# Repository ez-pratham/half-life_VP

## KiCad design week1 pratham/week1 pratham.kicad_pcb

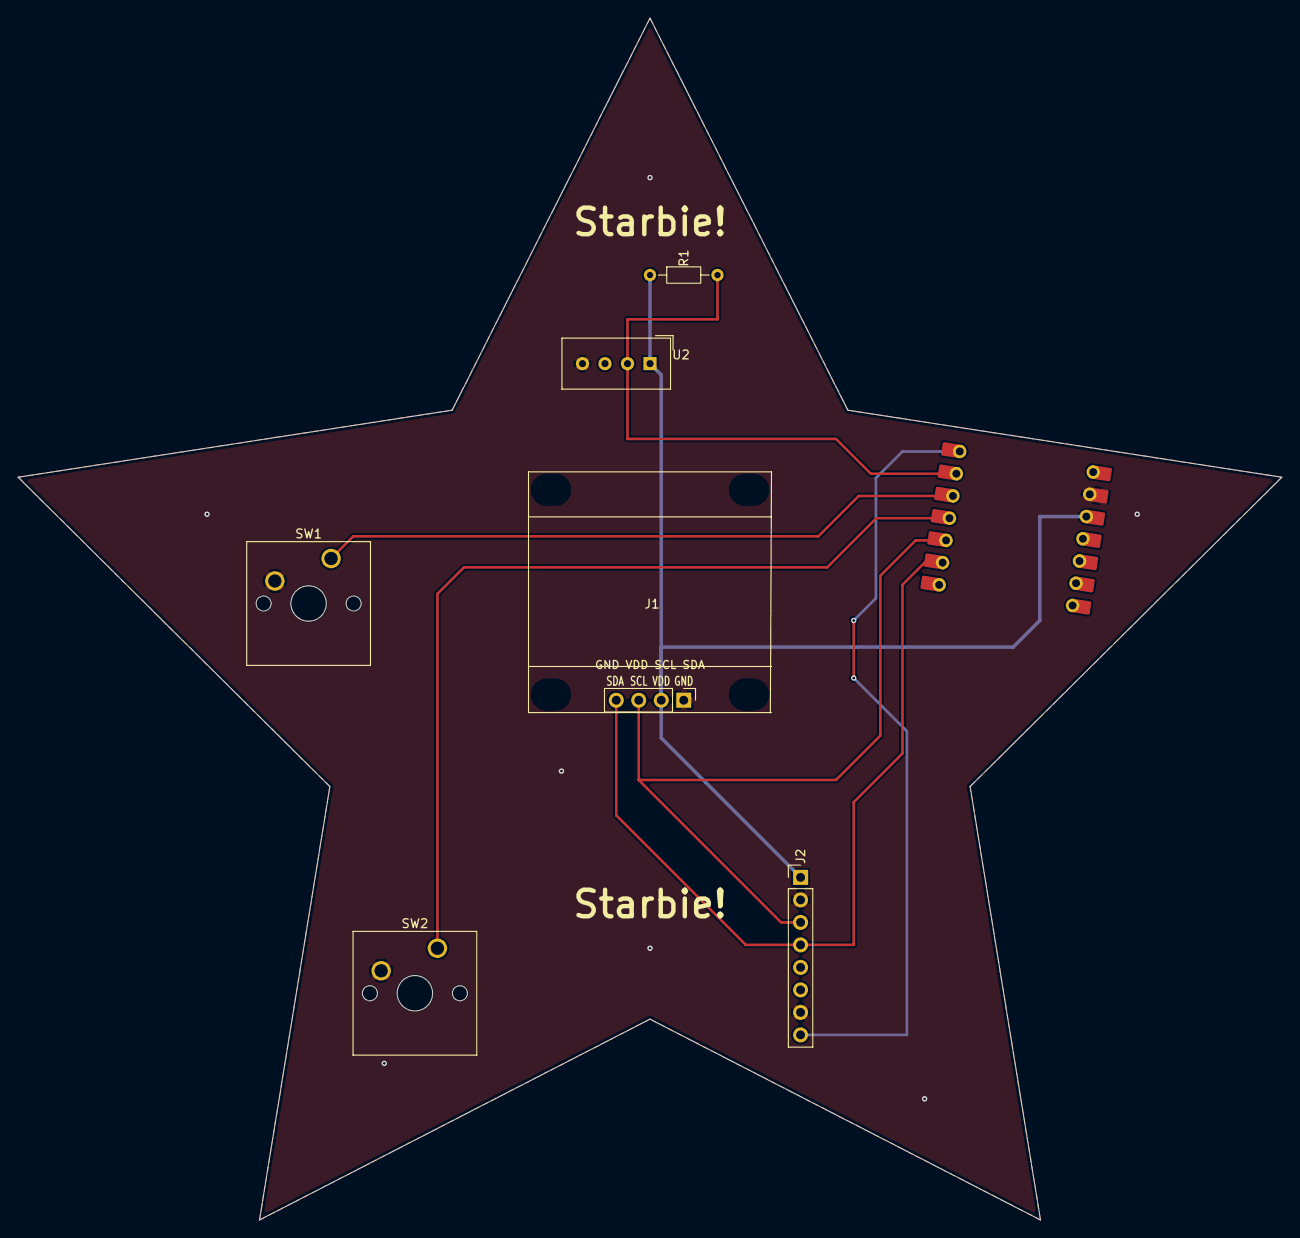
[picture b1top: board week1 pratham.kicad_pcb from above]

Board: 2 copper layers, 142.7 x 135.7 mm, 7 parts (0 on the bottom side), 8 nets.

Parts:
J1: OLED_0.96_I2C; Display_128x64_096_I2C
J2: GY-521_MPU6050; PinHeader_1x08_P2.54mm_Vertical
R1: 10K; R_Axial_DIN0204_L3.6mm_D1.6mm_P7.62mm_Horizontal
SW1, SW2: SW_Push; SW_Cherry_MX_1.00u_PCB
U1: XIAO-ESP32-C3-SMD; XIAO-ESP32-C6-DIP
U2: DHT11; Aosong_DHT11_5.5x12.0_P2.54mm

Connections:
+3.3V: J1.2, J2.1, R1.1, U1.12 (3V3_OUT), U2.1 (VDD)
/DHT11 DATA: R1.2, U1.2 (D1), U2.2 (DATA)
/GPIO2: SW1.1 (C), U1.3 (D2)
/GPIO3: SW2.1 (C), U1.4 (D3)
/MPU_INT: J2.8, U1.1 (D0)
/SCL: J1.3, J2.3, U1.5 (D4)
/SDA: J1.4, J2.4, U1.6 (D5)
GND: J1.1, J2.2, J2.7, SW1.2 (D), SW2.2 (D), U1.13 (GND), U2.4 (GND)
